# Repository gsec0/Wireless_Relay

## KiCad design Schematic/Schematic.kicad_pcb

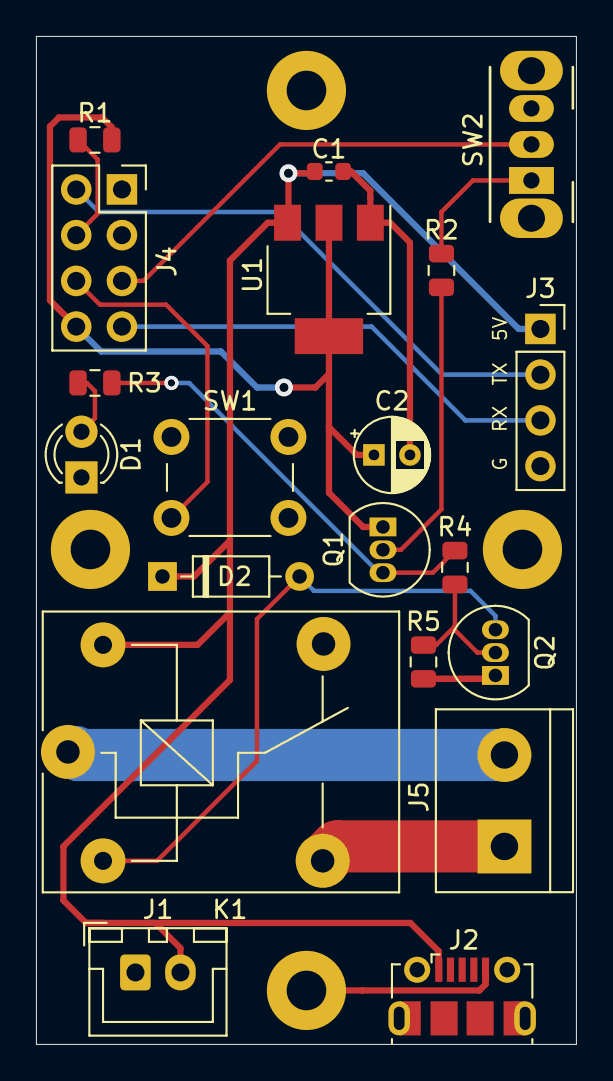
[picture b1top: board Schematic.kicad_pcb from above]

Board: 2 copper layers, 30.0 x 56.0 mm, 20 parts (0 on the bottom side), 16 nets.

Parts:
C1: 100nF; C_0603_1608Metric
C2: 10uF; CP_Radial_D4.0mm_P2.00mm
D1: R_LED; LED_D3.0mm
D2: 1N4148; D_DO-35_SOD27_P7.62mm_Horizontal
J1: PWR; JST_XH_B2B-XH-A_1x02_P2.50mm_Vertical
J2: USB_B_Micro; USB_Micro-B_Molex-105017-0001
J3: Debug_Port; PinSocket_1x04_P2.54mm_Vertical
J4: Conn_01x08_Female; PinSocket_2x04_P2.54mm_Vertical
J5: Screw_Terminal_01x02; TerminalBlock_bornier-2_P5.08mm
K1: SANYOU_SRD_Form_C; Relay_SPDT_SANYOU_SRD_Series_Form_C
Q1: S8550; TO-92_Inline
Q2: S8050; TO-92_Inline
R1: 510R; R_0805_2012Metric
R2: 300k; R_0805_2012Metric
R3: 100R; R_0805_2012Metric
R4: 1K; R_0805_2012Metric
R5: 10K; R_0805_2012Metric
SW1: SW_Push; SW_PUSH_6mm_H4.3mm
SW2: SW_SPDT; SW_CuK_OS102011MA1QN1_SPDT_Angled
U1: AMS1117-3.3; SOT-223-3_TabPin2

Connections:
+3V3: C2.1, J4.8, Q1.1, R1.2, U1.2
+5V: C1.1, D2.1, J1.2, J2.1, J3.1, K1.5, U1.3
/RX: J3.3, J4.7
/TX: J3.2, J4.2
GND: C1.2, C2.2, D1.1, J1.1, J2.5, J3.4, J4.1, Q2.1, R5.2, SW1.1, SW2.3, U1.1
unnamed: D1.2, R3.1
unnamed: D2.2, K1.2, Q2.3
unnamed: J4.4, R1.1
unnamed: J4.5, SW2.2
unnamed: J4.6, SW1.2
unnamed: J5.1, K1.3
unnamed: J5.2, K1.1
unnamed: Q1.2, R2.1
unnamed: Q1.3, R3.2, R4.1
unnamed: Q2.2, R4.2, R5.1
unnamed: R2.2, SW2.1
